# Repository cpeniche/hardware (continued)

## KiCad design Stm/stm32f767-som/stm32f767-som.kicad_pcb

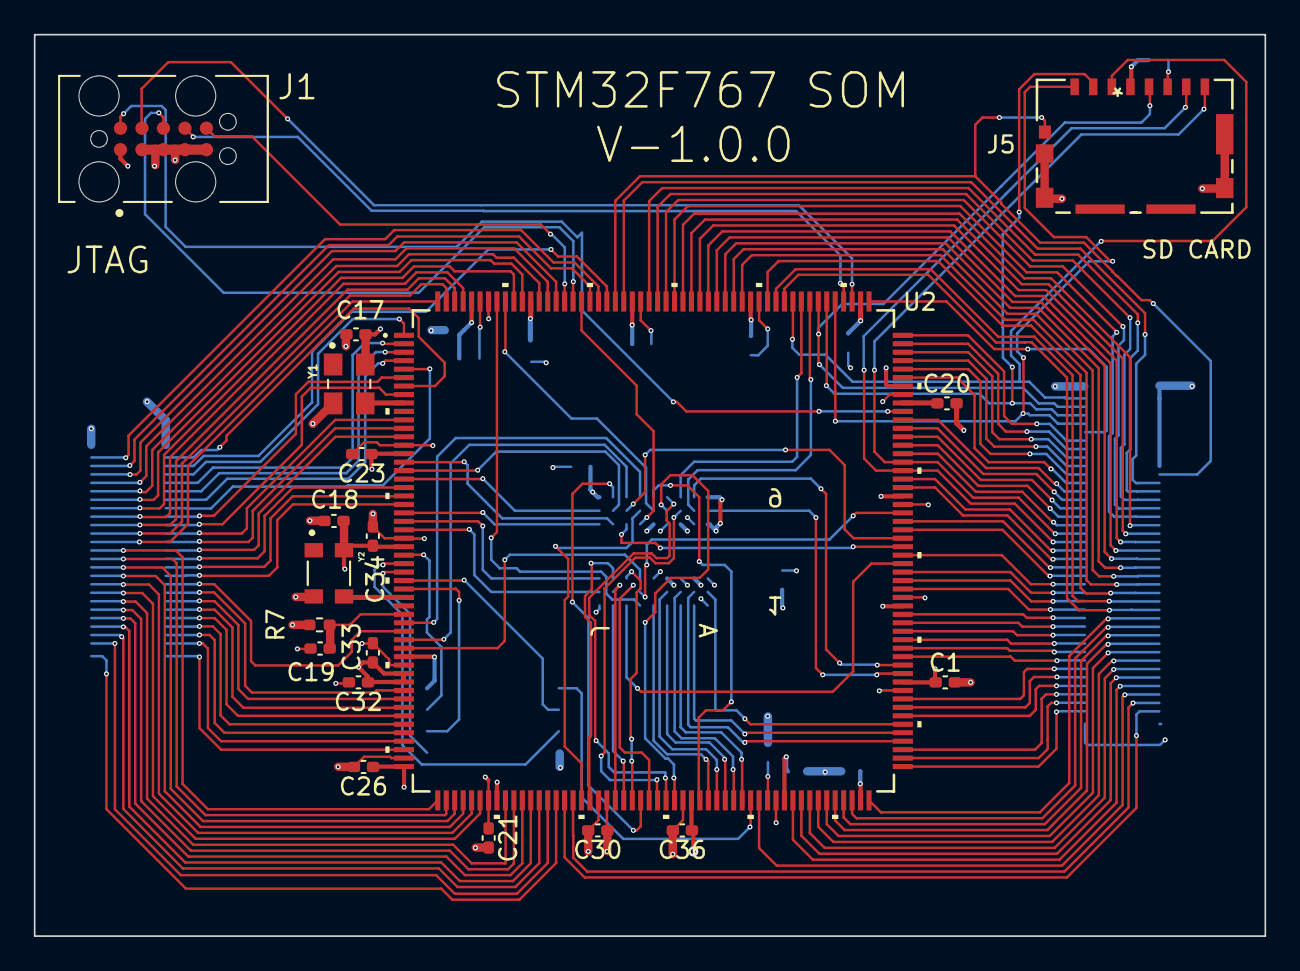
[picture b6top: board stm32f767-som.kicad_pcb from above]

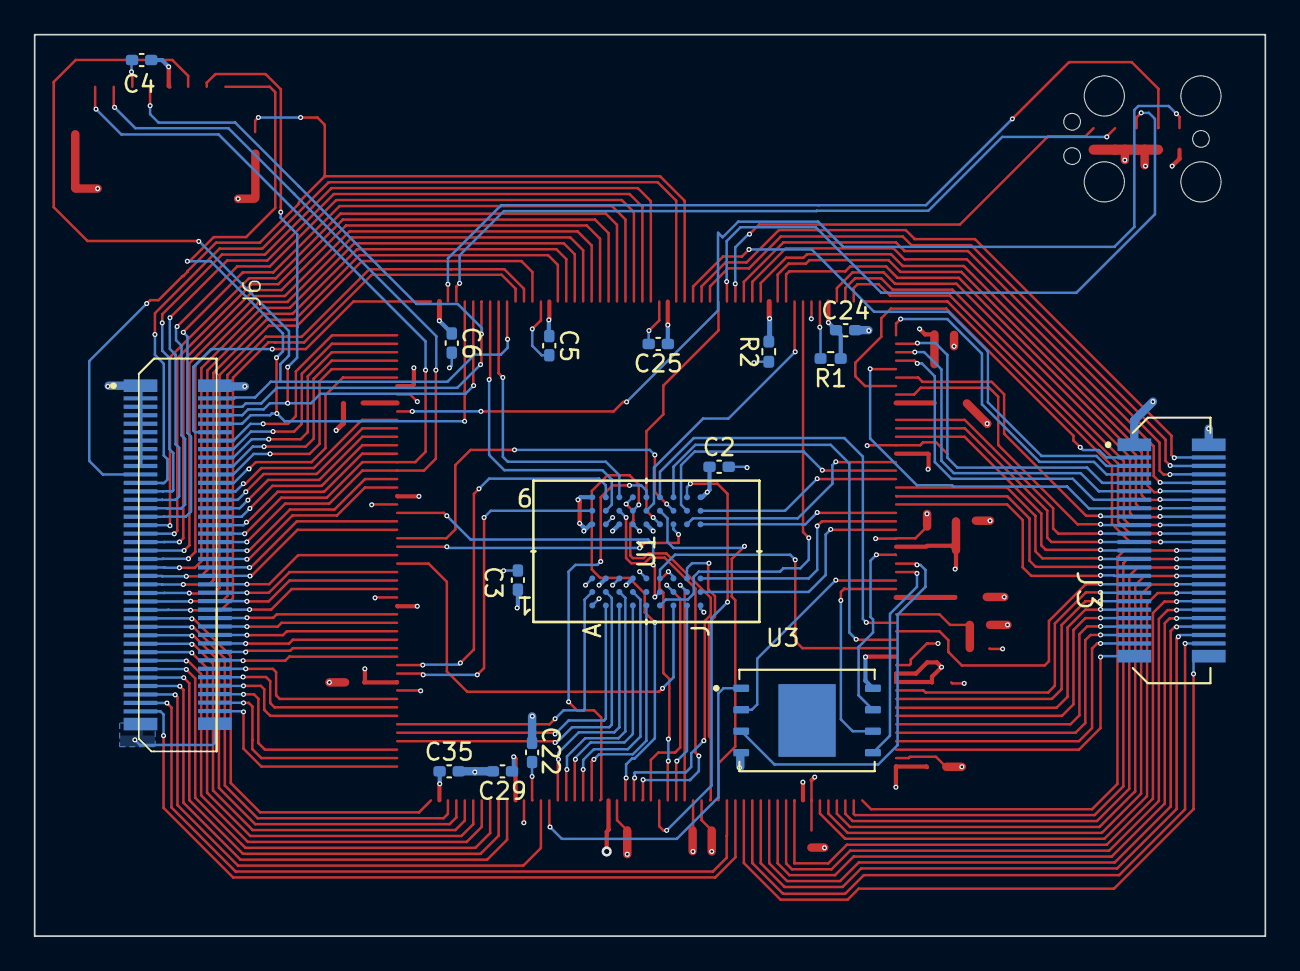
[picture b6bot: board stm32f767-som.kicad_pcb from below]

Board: 4 copper layers, 72.8 x 53.3 mm, 35 parts (16 on the bottom side), 175 nets.

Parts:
C1, C2, C3, C5, C6, C21, C23, C24, C25, C26, C29, C30, C32, C33, C34, C35, C36: 0.01uF; C_0402_1005Metric_Pad0.74x0.62mm_HandSolder
C4, C17, C18, C19: 0.1uF; C_0402_1005Metric_Pad0.74x0.62mm_HandSolder
C20, C22: 2.2uF; C_0402_1005Metric_Pad0.74x0.62mm_HandSolder
J1: TC2050-IDC-NL; TAG-CONNECT_TC2050-IDC
J3: AXK5S50037YG; PANASONIC_AXK5S50037YG
J5: 1051620001; 105162-0001_MOL
J6: AXK680347YG; PANASONIC-AXK5S80047YG
R1, R2, R7: 10K; R_0402_1005Metric_Pad0.72x0.64mm_HandSolder
U1: IS42S16320F-7BLI; IC54_IS42S16320F-7BLI_ISI
U2: LQFP-208_STM
U3: SON127P600X800X80-9N
Y1: ECS-327MVATX-3-CN-TR3; OSC_ECS-2333-160-BN-TR
Y2: ECS-TXO-3225-250-TR; OSC_ECS-TXO-3225-250-TR

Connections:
+3V3: C1.1, C2.1, C3.1, C4.2, C5.1, C6.1, C17.1, C18.1, C21.1, C23.1, C24.1, C25.1, C26.1, C29.1, C30.1, C32.1, C33.1, C34.1, C35.1, C36.1, J1.1 (VIN), J3.1, J5.P4 (VDD), J6.1, J6.2, J6.3, J6.5, J6.7, J6.9, J6.11, J6.13, J6.15, J6.17, J6.19, R1.1, R7.1, U1.A7 (VDDQ), U1.A9 (VDD), U1.B3 (VDDQ), U1.C7 (VDDQ), U1.D3 (VDDQ), U1.E7 (VDD), U1.J9 (VDD), U2.15 (VDD), U2.26 (VDD), U2.39 (VDD), U2.41 (VDDREF+), U2.42 (VDDA), U2.52 (VDD), U2.59 (VDD), U2.73 (VDD), U2.83 (VDD), U2.94 (VDD), U2.103 (VDD), U2.115 (VDD), U2.124 (VDD), U2.137 (VDDUSB), U2.150 (VDD), U2.158 (VDD), U2.171 (VDDSDMMC), U2.185 (VDD), U2.204 (VDD), U3.8 (VCC), Y1.4 (VDD), Y2.4 (VDD)
/Memory Interface/A0: U1.H7 (A0), U2.16 (FMC_A0)
/Memory Interface/A1: U1.H8 (A1), U2.17 (FMC_A1)
/Memory Interface/A2: U1.J8 (A2), U2.18 (FMC_A2)
/Memory Interface/A3: U1.J7 (A3), U2.22 (FMC_A3)
/Memory Interface/A4: U1.J3 (A4), U2.23 (FMC_A4)
/Memory Interface/A5: U1.J2 (A5), U2.24 (FMC_A5)
/Memory Interface/A6: U1.H3 (A6), U2.71 (FMC_A6)
/Memory Interface/A7: U1.H2 (A7), U2.74 (FMC_A7)
/Memory Interface/A8: U1.H1 (A8), U2.75 (FMC_A8)
/Memory Interface/A9: U1.G3 (A9), U2.76 (FMC_A9)
/Memory Interface/A10: U1.H9 (A10), U2.77 (FMC_A10)
/Memory Interface/A11: U1.G2 (A11), U2.78 (FMC_A11)
/Memory Interface/A12: U1.G1 (A12), U2.129 (FMC_A12)
/Memory Interface/A14: U1.G7 (BA0), U2.131 (FMC_A14/FMC_BA0)
/Memory Interface/A15: U1.G8 (BA1), U2.132 (FMC_A15/FMC_BA1)
/Memory Interface/CKE0: U1.F3 (CKE), U2.38 (FMC_SDCKE0)
/Memory Interface/CLK: U1.F2 (CLK), U2.135 (FMC_SDCLK)
/Memory Interface/D0: U1.A8 (DQ0), U2.116 (FMC_D0)
/Memory Interface/D1: U1.B9 (DQ1), U2.117 (FMC_D1)
/Memory Interface/D2: U1.B8 (DQ2), U2.164 (FMC_D2)
/Memory Interface/D3: U1.C9 (DQ3), U2.165 (FMC_D3)
/Memory Interface/D4: U1.C8 (DQ4), U2.79 (FMC_D4)
/Memory Interface/D5: U1.D9 (DQ5), U2.80 (FMC_D5)
/Memory Interface/D6: U1.D8 (DQ6), U2.81 (FMC_D6)
/Memory Interface/D7: U1.E9 (DQ7), U2.84 (FMC_D7)
/Memory Interface/D8: U1.E1 (DQ8), U2.85 (FMC_D8)
/Memory Interface/D9: U1.D2 (DQ9), U2.86 (FMC_D9)
/Memory Interface/D10: U1.D1 (DQ10), U2.87 (FMC_D10)
/Memory Interface/D11: U1.C2 (DQ11), U2.88 (FMC_D11)
/Memory Interface/D12: U1.C1 (DQ12), U2.89 (FMC_D12)
/Memory Interface/D13: U1.B2 (DQ13), U2.108 (FMC_D13)
/Memory Interface/D14: U1.B1 (DQ14), U2.109 (FMC_D14)
/Memory Interface/D15: U1.A2 (DQ15), U2.110 (FMC_D15)
/Memory Interface/DQMH: U1.F1 (DQMH), U2.201 (~FMC_BL1)
/Memory Interface/DQML: U1.E8 (DQML), U2.200 (~FMC_BL0)
/Memory Interface/~CAS: U1.F7 (~CAS), U2.191 (~FMC_SDCAS)
/Memory Interface/~CS0: U1.G9 (~CS), U2.37 (~FMC_SDE0)
/Memory Interface/~QUAD_CS: U2.90 (~QUADSPI_BK1_CS), U3.1 (~CS)
/Memory Interface/~RAS: U1.F8 (~RAS), U2.70 (~FMC_SDRAS)
/Memory Interface/~WE: U1.F9 (~WE), U2.35 (~FMC_SDWE)
/Peripherals/BOOT0: R2.2, U2.197 (BOOT0)
/Peripherals/ETH_CRS_DV: J3.32, U2.56 (ETH_CRS_DV)
/Peripherals/ETH_MDC: J3.33, U2.36 (ETH_MDC)
/Peripherals/ETH_MDIO: J3.39, U2.45 (ETH_MDIO)
/Peripherals/ETH_REF_CLK: J3.37, U2.44 (ETH_REF_CLK)
/Peripherals/ETH_RXD0: J3.34, U2.57 (ETH_RXD0)
/Peripherals/ETH_RXD1: J3.36, U2.58 (ETH_RXD1)
/Peripherals/ETH_TXD0: J6.55, U2.104 (ETH_TXD0)
/Peripherals/ETH_TXD1: J6.78, U2.105 (ETH_TXD1)
/Peripherals/ETH_TX_EN: J6.73, U2.91 (ETH_TX_EN)
/Peripherals/LCD_B0: J6.43, U2.174 (LCD_B0)
/Peripherals/LCD_B1: J6.41, U2.175 (LCD_B1)
/Peripherals/LCD_B2: J6.47, U2.172 (LCD_B2)
/Peripherals/LCD_B3: J6.37, U2.177 (LCD_B3)
/Peripherals/LCD_B4: J6.29, U2.181 (LCD_B4)
/Peripherals/LCD_B5: J3.49, U2.50 (LCD_B5)
/Peripherals/LCD_B6: J3.5, U2.188 (LCD_B6)
/Peripherals/LCD_B7: J3.4, U2.189 (LCD_B7)
/Peripherals/LCD_CLK: J3.31, U2.21 (LCD_CLK)
/Peripherals/LCD_DE: J3.6, U2.190 (LCD_DE)
/Peripherals/LCD_G0: J3.40, U2.62 (LCD_G0)
/Peripherals/LCD_G1: J3.38, U2.61 (LCD_G1)
/Peripherals/LCD_G2: J3.30, U2.55 (LCD_G2)
/Peripherals/LCD_G3: J6.58, U2.122 (LCD_G3)
/Peripherals/LCD_G4: J6.56, U2.123 (LCD_G4)
/Peripherals/LCD_G5: J3.45, U2.48 (LCD_G5)
/Peripherals/LCD_G6: J3.25, U2.13 (LCD_G6)
/Peripherals/LCD_G7: J6.50, U2.128 (LCD_G7)
/Peripherals/LCD_HSYNC: J3.23, U2.12 (LCD_HSYNC)
/Peripherals/LCD_R0: J3.41, U2.46 (LCD_R0)
/Peripherals/LCD_R1: J3.43, U2.47 (LCD_R1)
/Peripherals/LCD_R2: J3.48, U2.66 (LCD_R2)
/Peripherals/LCD_R3: J3.50, U2.67 (LCD_R3)
/Peripherals/LCD_R4: J3.28, U2.54 (LCD_R4)
/Peripherals/LCD_R5: J6.75, U2.69 (LCD_R5)
/Peripherals/LCD_R6: J6.71, U2.95 (LCD_R6)
/Peripherals/LCD_R7: J3.46, U2.65 (LCD_R7)
/Peripherals/LCD_VSYNC: J3.21, U2.11 (LCD_VSYNC)
/Peripherals/PA4: J3.26, U2.53 (PA4)
/Peripherals/PB0: J3.35, U2.43 (PA0/WKUP)
/Peripherals/PB2: J3.42, U2.63 (PB2)
/Peripherals/PB5: J3.8, U2.194 (PB5)
/Peripherals/PB6: J3.10, U2.195 (PB6)
/Peripherals/PB8: J3.14, U2.198 (PB8)
/Peripherals/PB9: J3.16, U2.199 (PB9)
/Peripherals/PB14: J6.76, U2.106 (PB14)
/Peripherals/PB15: J6.74, U2.107 (PB15)
/Peripherals/PC6: J6.42, U2.138 (PC6)
/Peripherals/PC13: J3.19, U2.8 (PC13)
/Peripherals/PD3: J6.53, U2.167 (PD3)
/Peripherals/PD7: J6.45, U2.173 (PD7)
/Peripherals/PG6: J6.46, U2.133 (PG6)
/Peripherals/PG7: J6.44, U2.134 (PG7)
/Peripherals/PG9: J6.35, U2.178 (PG9)
/Peripherals/PG10: J6.33, U2.179 (PG10)
/Peripherals/PG11: J6.31, U2.180 (PG11)
/Peripherals/PG14: J6.25, U2.183 (PG14)
/Peripherals/PH5: J3.47, U2.49 (PH5)
/Peripherals/PH8: J6.65, U2.98 (PH8)
/Peripherals/PH9: J6.63, U2.99 (PH9)
/Peripherals/PH10: J6.61, U2.100 (PH10)
/Peripherals/PH11: J6.59, U2.101 (PH11)
/Peripherals/PH12: J6.57, U2.102 (PH12)
/Peripherals/PH13: J6.24, U2.151 (PH13)
/Peripherals/PH14: J6.22, U2.152 (PH14)
/Peripherals/PH15: J6.20, U2.153 (PH15)
/Peripherals/PI0: J6.18, U2.154 (PI0)
/Peripherals/PI1: J6.16, U2.155 (PI1)
/Peripherals/PI2: J6.14, U2.156 (PI2)
/Peripherals/PI3: J6.12, U2.157 (PI3)
/Peripherals/PI4: J3.18, U2.205 (PI4)
/Peripherals/PI5: J3.20, U2.206 (PI5)
/Peripherals/PI6: J3.22, U2.207 (PI6)
/Peripherals/PI7: J3.24, U2.208 (PI7)
/Peripherals/PI8: J3.3, U2.7 (PI8)
/Peripherals/PI12: J3.27, U2.19 (PI12)
/Peripherals/PI13: J3.29, U2.20 (PI13)
/Peripherals/PI15: J3.44, U2.64 (PI15)
/Peripherals/PJ3: J6.77, U2.68 (PJ3)
/Peripherals/PJ6: J6.66, U2.118 (PJ6)
/Peripherals/PJ7: J6.64, U2.119 (PJ7)
/Peripherals/PJ8: J6.62, U2.120 (PJ8)
/Peripherals/PJ9: J6.60, U2.121 (PJ9)
/Peripherals/PJ14: J6.39, U2.176 (PJ14)
/Peripherals/PK0: J6.54, U2.126 (PK0)
/Peripherals/PK1: J6.52, U2.127 (PK1)
/Peripherals/PK3: J6.23, U2.186 (PK3)
/Peripherals/TDI: J1.6 (SWO/TDO), U2.192 (TDO_SW0)
/Peripherals/TMS_SWCLK: J1.4 (SWDCLK/TCK), U2.159 (TCK_SWCLK)
/Peripherals/TMS_SWDIO: J1.2 (SWDIO/TMS), U2.147 (TMS_SWDIO)
/Peripherals/TMS_SWO: J1.8 (TDI), U2.160 (TDI)
/Peripherals/USB_DM: J6.28, U2.145 (USB_OTG_FS_DM)
/Peripherals/USB_DP: J6.26, U2.146 (USB_OTG_FS_DP)
/Peripherals/USB_ID: J6.30, U2.144 (USB_OTG_FS_ID)
/Peripherals/USB_SOF: J6.34, U2.142 (USB_OTG_FS_SOF)
/Peripherals/USB_VBUS: J6.32, U2.143 (USB_OTG_FS_VBUS)
/Peripherals/~TRST: J1.10 (~RESET), U2.193 (TRST)
/Power/~RESET: C19.1, R7.2, U2.34 (~RESET)
GND: C1.2, C2.2, C3.2, C5.2, C6.2, C17.2, C18.2, C19.2, C20.2, C21.2, C22.2, C23.2, C24.2, C25.2, C26.2, C29.2, C30.2, C32.2, C33.2, C34.2, C35.2, C36.2, J1.3 (GND), J1.5 (GND), J1.7 (GND), J1.9 (GND), J3.2, J5.G1 (GND), J5.G2 (GND), J5.G3 (GND), J5.G4 (GND), J6.79, J6.80, R2.1, U1.A1 (VSS), U1.A3 (VSSQ), U1.B7 (VSSQ), U1.C3 (VSSQ), U1.D7 (VSSQ), U1.E3 (VSS), U1.J1 (VSS), U2.14 (VSS), U2.25 (VSS), U2.40 (VSSA), U2.51 (VSS), U2.60 (VSS), U2.72 (VSS), U2.82 (VSS), U2.93 (VSS), U2.114 (VSS), U2.125 (VSS), U2.136 (VSS), U2.149 (VSS), U2.170 (VSS), U2.184 (VSS), U2.202 (VSS), U3.4 (GND), Y1.2 (GND), Y2.2 (GND)
unnamed: C4.1, J5.P6 (VSS)
unnamed: R1.2, U2.203 (PDRON)
unnamed: C22.1, U2.92 (VCAP_1)
unnamed: C20.1, U2.148 (VCAP_2)
unnamed: U2.29 (QUADSPI_BK1_IO0), U3.5 (DI/IO_{0})
unnamed: U2.30 (QUADSPI_BK1_IO1), U3.2 (D0/IO_{1})
unnamed: U2.28 (QUADSPI_BK1_IO2), U3.3 (~WP/IO_{2})
unnamed: U2.27 (QUADSPI_BK1_IO3), U3.7 (~HOLD/IO_{3})
unnamed: U2.31 (QUADSPI_CLK), U3.6 (CLK)
unnamed: U2.9 (RCC_OSC32_IN), Y1.3 (OUTPUT)
unnamed: U2.32 (RCC_OSC_IN), Y2.3 (OUTPUT)
PB7: J3.12, U2.196 (PB7)
PC7: J6.40, U2.139 (PC7)
PD4: J6.51, U2.168 (PD4)
PD5: J6.49, U2.169 (PD5)
PD11: J6.72, U2.111 (PD11)
PD12: J6.70, U2.112 (PD12)
PD13: J6.68, U2.113 (PD13)
PE2: J3.7, U2.1 (PE2)
PE3: J3.9, U2.2 (PE3)
PE4: J3.11, U2.3 (PE4)
PE5: J3.13, U2.4 (PE5)
PE6: J3.15, U2.5 (PE6)
PG3: J6.48, U2.130 (PG3)
PG13: J6.27, U2.182 (PG13)
PH6: J6.69, U2.96 (PH6)
PH7: J6.67, U2.97 (PH7)
PK4: J5.P9 (DET), J6.21, U2.187 (PK4)
SMMC1_CK: J5.P5 (CLK), J6.6, U2.163 (SDMMC1_CK)
SMMC1_CMD: J5.P3 (CMD), J6.4, U2.166 (SDMMC1_CMD)
SMMC1_D0: J5.P7 (DAT0), J6.38, U2.140 (SDMMC1_D0)
SMMC1_D1: J5.P8 (DAT1), J6.36, U2.141 (SDMMC1_D1)
SMMC1_D2: J5.P1 (DAT2), J6.10, U2.161 (SDMMC1_D2)
SMMC1_D3: J5.P2 (CD/DAT3), J6.8, U2.162 (SDMMC1_D3)
VBAT: J3.17, U2.6 (VBAT)
